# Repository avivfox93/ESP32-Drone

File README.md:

## ESP32-Drone Hardware

### Introduction

Hardware design for drone based of ESP32 and BME6050. It desinged using KiCad 6. Parts chosen for both low cost and stocks availability.

### Features

1. ESP32 MCU
2. MPU6050 IMU
3. BMP280 barometer
4. LiPo charger
5. WS2812b indication LED
6. External peripherals extension connector
7. On board 8mm motor sockets

### Remarks
1. Better to manufacure PCB 1.0 mm in thickness
2. Better to solder the motor on both sides, motors might tear the copper layer if its not soldered well

### Firmware
Can be used with my fork of ESP-Drone (based on Crazyflie) -> https://github.com/avivfox93/esp-drone

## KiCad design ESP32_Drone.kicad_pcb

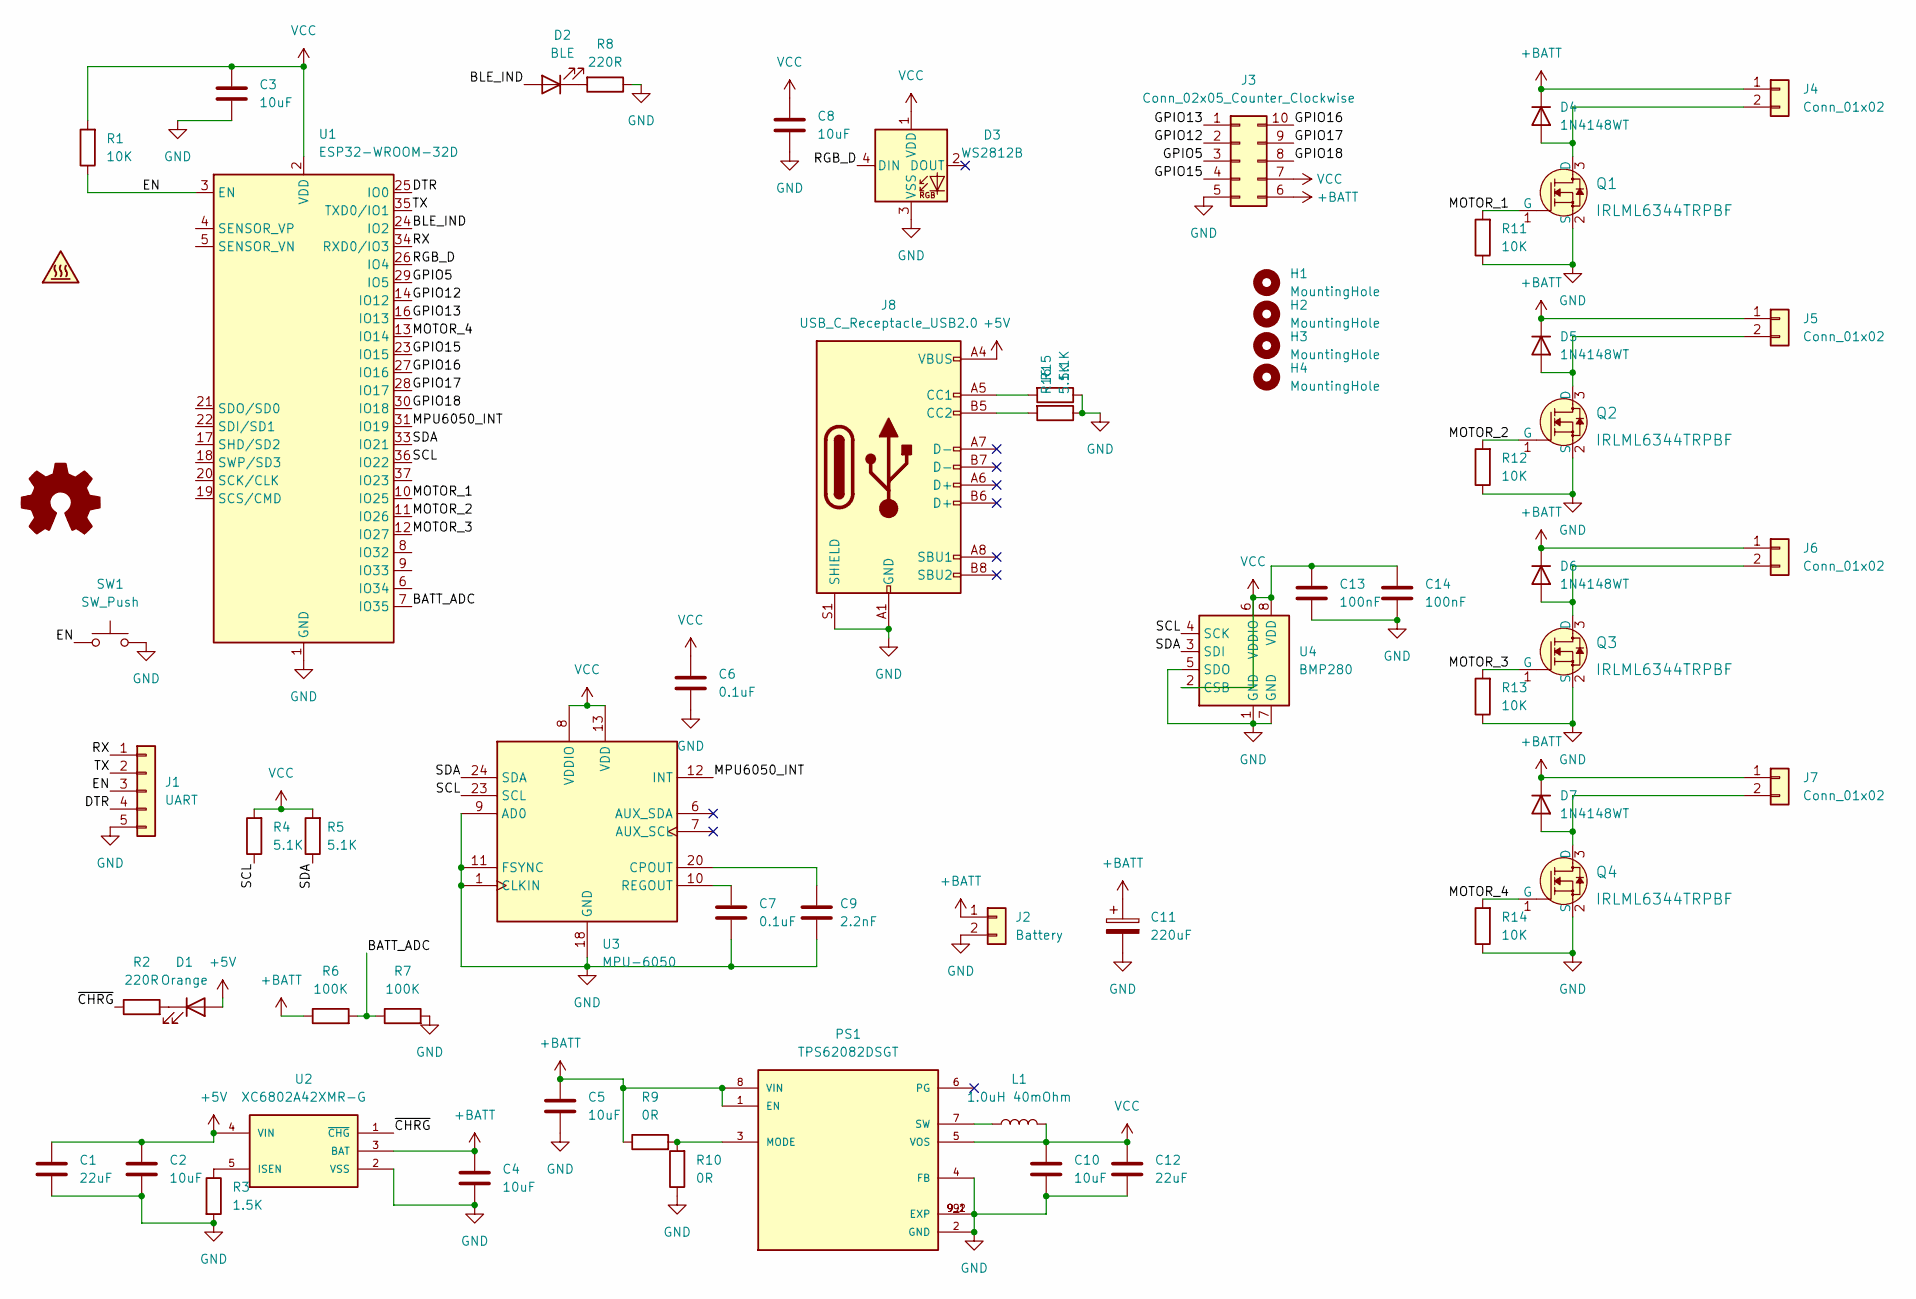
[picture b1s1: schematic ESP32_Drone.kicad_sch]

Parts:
C1, C12: 22uF; C_0603_1608Metric
C2, C3, C4, C5, C8, C10: 10uF; C_0603_1608Metric
C6, C7: 0.1uF; C_0603_1608Metric
C9: 2.2nF; C_0603_1608Metric
C11: 220uF; CP_Radial_D5.0mm_P2.50mm
C13, C14: 100nF; C_0603_1608Metric
D1: Orange; LED_0603_1608Metric
D2: BLE; LED_0603_1608Metric
D3: WS2812B; LED_WS2812B_PLCC4_5.0x5.0mm_P3.2mm
D4, D5, D6, D7: 1N4148WT; D_SOD-523
H1, H2, H3, H4: MountingHole; MountingHole_3.2mm_M3
J1: UART; PinHeader_1x05_P2.54mm_Vertical
J2: Battery; JST_XH_B2B-XH-AM_1x02_P2.50mm_Vertical
J3: Conn_02x05_Counter_Clockwise; PinSocket_2x05_P2.54mm_Vertical
J4, J5, J6, J7: Conn_01x02; PinSocket_1x02_P2.54mm_Vertical
J8: USB_C_Receptacle_USB2.0; USB_C_Receptacle_HRO_TYPE-C-31-M-12
L1: 1.0uH 40mOhm; L_0805_2012Metric
LOGO1: Logo_Open_Hardware_Small; meshek_fox_logo.kicad_5.9X6.0_mod
PS1: TPS62082DSGT; CONV_TPS62082DSGT; PARTREV NOVEMBER 2016
Q1, Q2, Q3, Q4: IRLML6344TRPBF; SOT-23-3; MPN IRLML6344TRPBF; Digi-Key_PN IRLML6344TRPBFCT-ND
R1, R11, R12, R13, R14: 10K; R_0603_1608Metric
R2, R8: 220R; R_0603_1608Metric
R3: 1.5K; R_0603_1608Metric
R4, R5, R15, R16: 5.1K; R_0603_1608Metric
R6, R7: 100K; R_0603_1608Metric
R9, R10: 0R; R_0603_1608Metric
SW1: SW_Push; SW_Push_SPST_NO_Alps_SKRK
SYM1: SYM_Hot_Small; PCB Drone Edgecuts
U1: ESP32-WROOM-32D; ESP32-WROOM-32
U2: XC6802A42XMR-G; SOT95P280X130-5N
U3: MPU-6050; InvenSense_QFN-24_4x4mm_P0.5mm
U4: BMP280; Bosch_LGA-8_2x2.5mm_P0.65mm_ClockwisePinNumbering

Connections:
+5V: C1.1, C2.1, D1.2 (A), J8.A4 (VBUS), J8.A9 (VBUS), J8.B4 (VBUS), J8.B9 (VBUS), U2.4 (VIN)
+BATT: C4.1, C5.1, C11.1, D4.1 (K), D5.1 (K), D6.1 (K), D7.1 (K), J2.1, J3.6, J4.1, J5.1, J6.1, J7.1, PS1.1 (EN), PS1.8 (VIN), R6.1, R9.1, U2.3 (BAT)
/BATT_ADC: R6.2, R7.1, U1.7 (IO35)
/BLE_IND: D2.2 (A), U1.24 (IO2)
/DTR: J1.4, U1.25 (IO0)
/EN: J1.3, R1.1, SW1.1, U1.3 (EN)
/GPIO5: J3.3, U1.29 (IO5)
/GPIO12: J3.2, U1.14 (IO12)
/GPIO13: J3.1, U1.16 (IO13)
/GPIO15: J3.4, U1.23 (IO15)
/GPIO16: J3.10, U1.27 (IO16)
/GPIO17: J3.9, U1.28 (IO17)
/GPIO18: J3.8, U1.30 (IO18)
/MOTOR_1: Q1.1 (G), R11.2, U1.10 (IO25)
/MOTOR_2: Q2.1 (G), R12.2, U1.11 (IO26)
/MOTOR_3: Q3.1 (G), R13.2, U1.12 (IO27)
/MOTOR_4: Q4.1 (G), R14.2, U1.13 (IO14)
/MPU6050_INT: U1.31 (IO19), U3.12 (INT)
/RGB_D: D3.4 (DIN), U1.26 (IO4)
/RX: J1.1, U1.34 (RXD0/IO3)
/SCL: R4.1, U1.36 (IO22), U3.23 (SCL), U4.4 (SCK)
/SDA: R5.1, U1.33 (IO21), U3.24 (SDA), U4.3 (SDI)
/TX: J1.2, U1.35 (TXD0/IO1)
/~CHRG: R2.1, U2.1 (~CHG)
GND: C1.2, C2.2, C3.2, C4.2, C5.2, C6.2, C7.2, C8.2, C9.2, C10.2, C11.2, C12.2, C13.2, C14.2, D3.3 (VSS), J1.5, J2.2, J3.5, J8.A1 (GND), J8.A12 (GND), J8.B1 (GND), J8.B12 (GND), J8.S1 (SHIELD), PS1.2 (GND), PS1.4 (FB), PS1.9 (EXP), PS1.9_1 (EXP), PS1.9_2 (EXP), Q1.2 (S), Q2.2 (S), Q3.2 (S), Q4.2 (S), R3.2, R7.2, R8.1, R10.1, R11.1, R12.1, R13.1, R14.1, R15.1, R16.1, SW1.2, U1.1 (GND), U1.15 (GND), U1.38 (GND), U1.39 (GND), U2.2 (VSS), U3.1 (CLKIN), U3.9 (AD0), U3.11 (FSYNC), U3.18 (GND), U4.1 (GND), U4.5 (SDO), U4.7 (GND)
unnamed: C7.1, U3.10 (REGOUT)
unnamed: C9.1, U3.20 (CPOUT)
unnamed: D1.1 (K), R2.2
unnamed: D2.1 (K), R8.2
unnamed: D4.2 (A), J4.2, Q1.3 (D)
unnamed: D5.2 (A), J5.2, Q2.3 (D)
unnamed: D6.2 (A), J6.2, Q3.3 (D)
unnamed: D7.2 (A), J7.2, Q4.3 (D)
unnamed: J8.A5 (CC1), R15.2
unnamed: J8.B5 (CC2), R16.2
unnamed: L1.1, PS1.7 (SW)
unnamed: PS1.3 (MODE), R9.2, R10.2
unnamed: R3.1, U2.5 (ISEN)
VCC: C3.1, C6.1, C8.1, C10.1, C12.1, C13.1, C14.1, D3.1 (VDD), J3.7, L1.2, PS1.5 (VOS), R1.2, R4.2, R5.2, U1.2 (VDD), U3.8 (VDDIO), U3.13 (VDD), U4.2 (CSB), U4.6 (VDDIO), U4.8 (VDD)

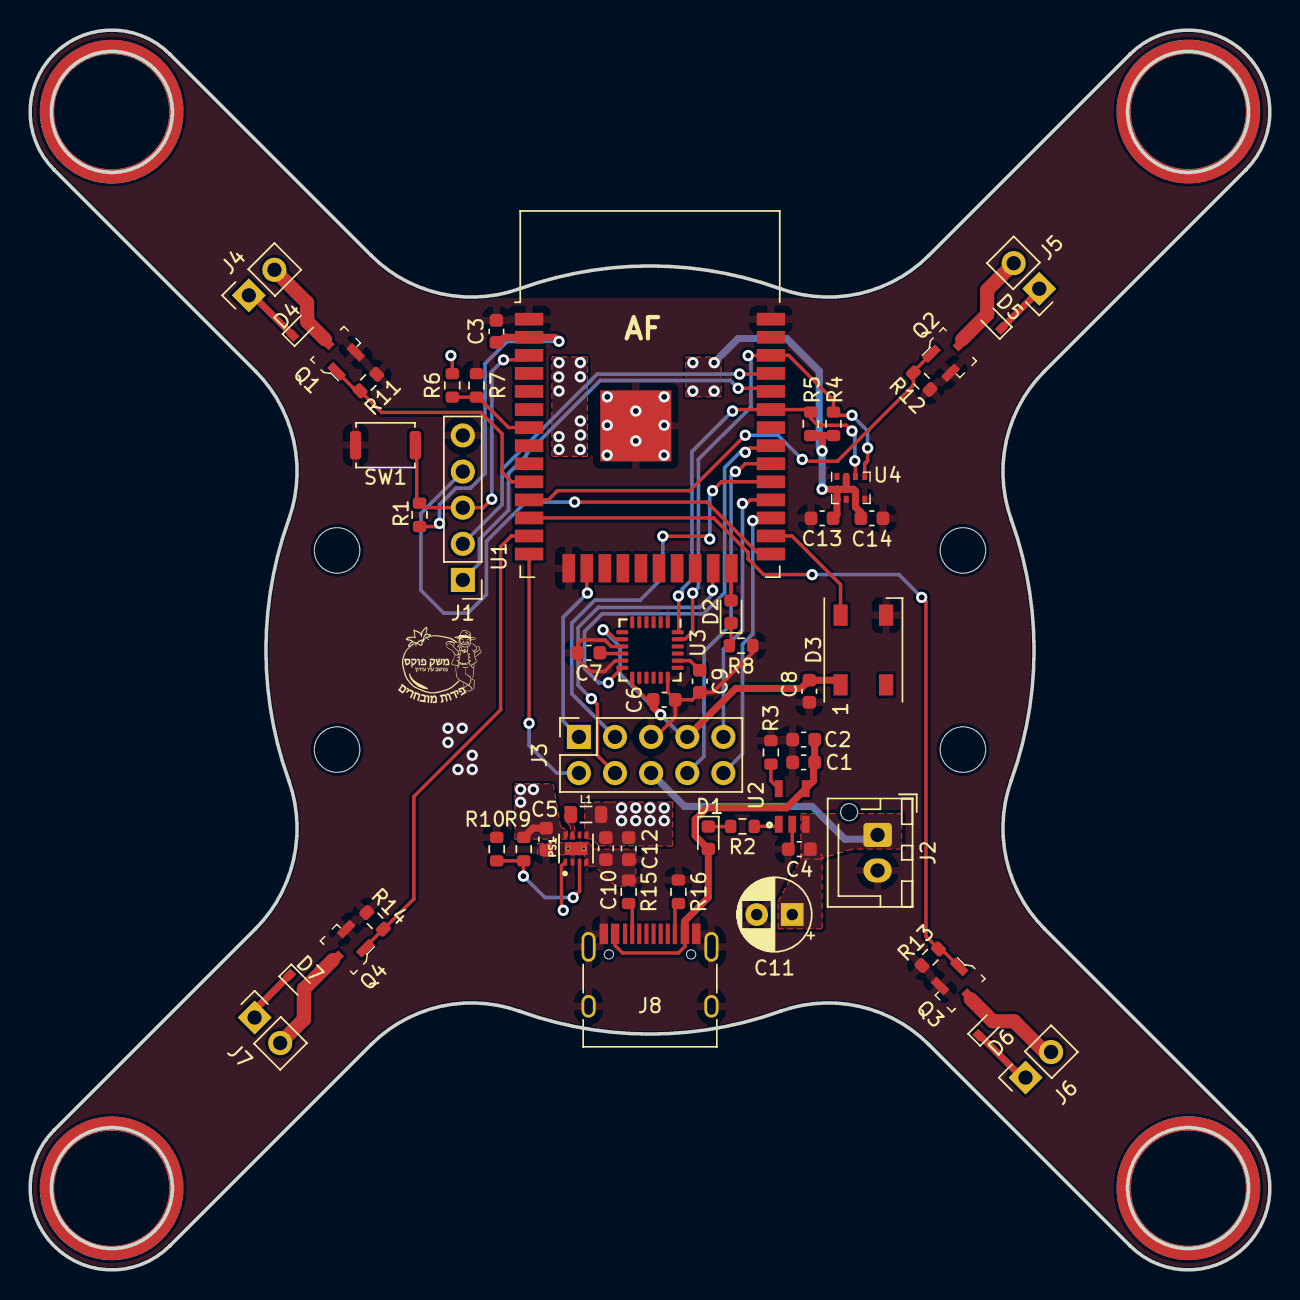
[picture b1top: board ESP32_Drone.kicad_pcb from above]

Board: 2 copper layers, 87.1 x 87.1 mm, 62 parts (0 on the bottom side), 39 nets.

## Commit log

2022-09-28 init
2022-09-28 Update README.md
    typo
